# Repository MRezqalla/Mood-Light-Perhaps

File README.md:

# Mood-Light-Perhaps
## This project concerns a mood light arduino device that can change moods. 
### Maybe in the future expand it so it's perhaps.

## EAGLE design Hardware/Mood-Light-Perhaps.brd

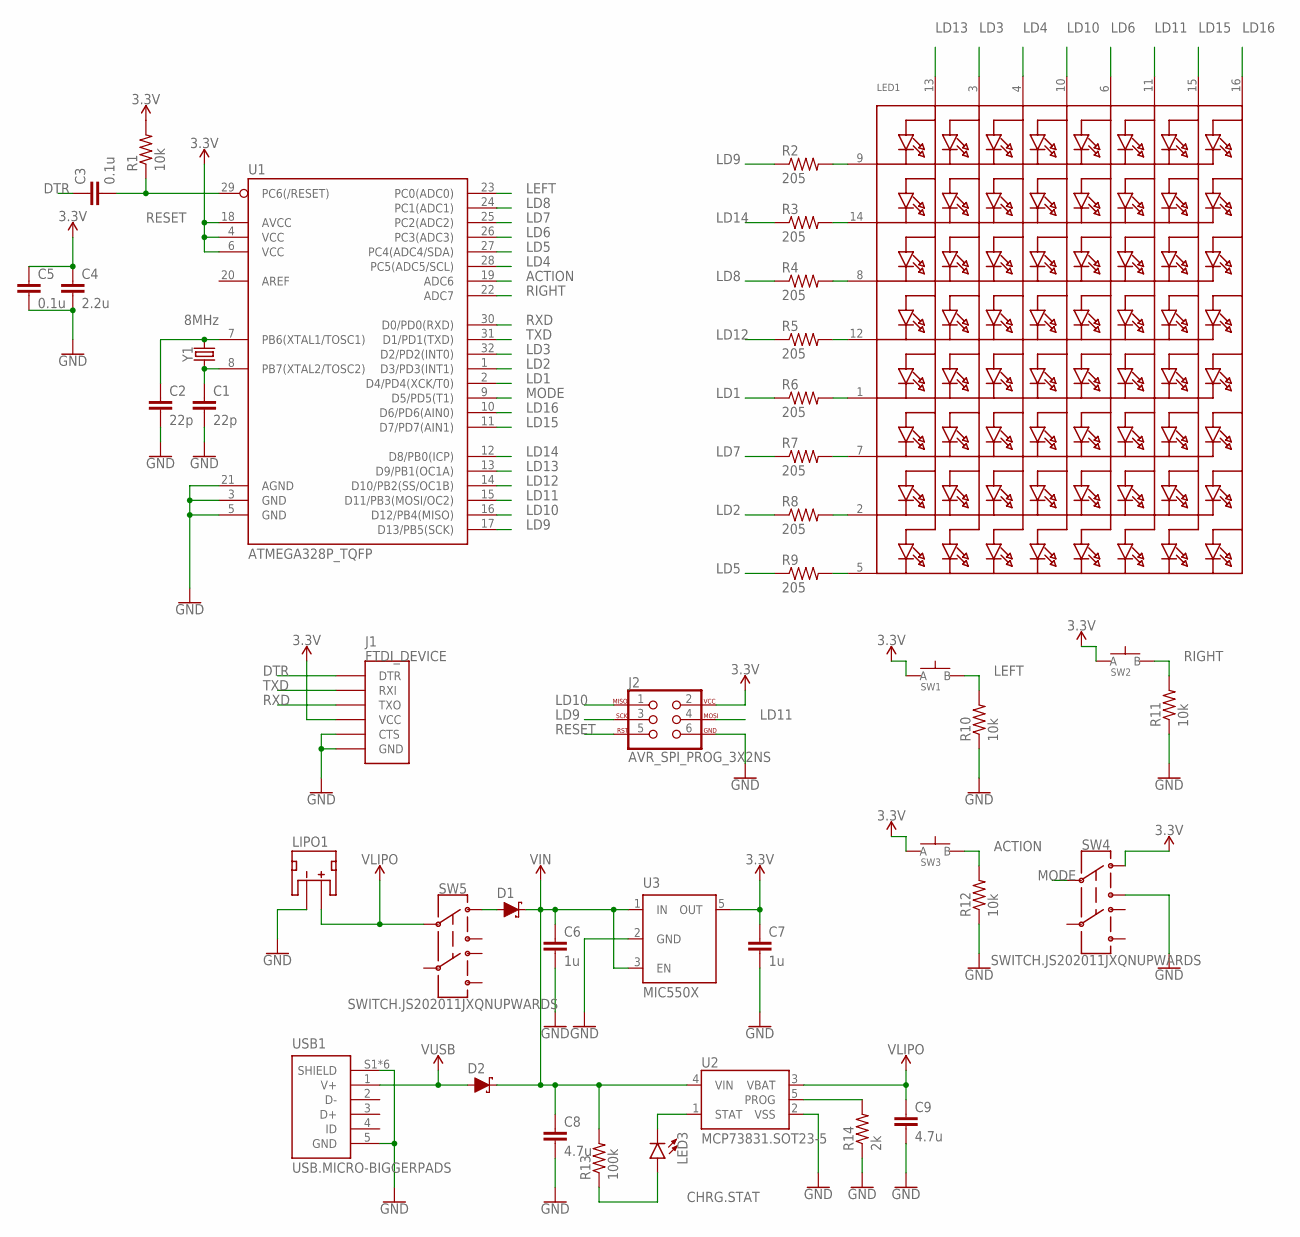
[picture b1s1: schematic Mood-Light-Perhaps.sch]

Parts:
C1, C2: 22p; C0603
C3, C5: 0.1u; C0603
C4: 2.2u; C0603
C6, C7: 1u; C0603
C8, C9: 4.7u; C0603
D1, D2: SCHOTTKY-USC; USC
J1: FTDI_DEVICE
J2: AVR_SPI_PROG_3X2NS; 2X3-NS
LED1: DOTMATRIX_8X8_ROWCATHODEM12A881UR; DOTMATRIX_BL-M12A881UR
LED3: LED0805; LED-0805
LIPO1: JST_2MM_MALE; JST-2-SMD
R1, R10, R11, R12: 10k; R0603
R2, R3, R4, R5, R6, R7, R8, R9: 205; R0603
R13: 100k; R0603
R14: 2k; R0603
SW1, SW2, SW3: SPST.KT11P4SM34LFS
SW4, SW5: SWITCH.JS202011JXQNUPWARDS; SWITCH.00
U1: ATMEGA328P_TQFP; TQFP32-08
U2: MCP73831.SOT23-5; SOT23-5
U3: MIC550X; SOT23-5
USB1: USB.MICRO-BIGGERPADS; USB-MICRO-01.BIGGERPADS
Y1: 8MHz; CA-301

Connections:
3.3V: C4.1, C5.1, C7.1, J1.VCC, J2.2, R1.2, SW1.1 (A), SW1.2 (A), SW2.1 (A), SW2.2 (A), SW3.1 (A), SW3.2 (A), SW4.1, U1.4 (VCC), U1.6 (VCC), U1.18 (AVCC), U3.5 (OUT)
ACTION: R12.2, SW3.3 (B), SW3.4 (B), U1.19 (ADC6)
CHRG.STAT: LED3.A, R13.1
DTR: C3.1, J1.DTR
GND: C1.2, C2.2, C4.2, C5.2, C6.2, C7.2, C8.2, C9.2, J1.CTS, J1.GND, J2.6, LIPO1.1 (-), R10.1, R11.1, R12.1, R14.1, SW4.3, U1.3 (GND), U1.5 (GND), U1.21 (AGND), U2.2 (VSS), U3.2 (GND), USB1.5 (GND), USB1.S1 (SHIELD), USB1.S2 (SHIELD), USB1.S3 (SHIELD), USB1.S4 (SHIELD), USB1.S5 (SHIELD), USB1.S6 (SHIELD)
LD1: R6.1, U1.2 (D4/PD4(XCK/T0))
LD2: R8.1, U1.1 (D3/PD3(INT1))
LD3: LED1.3 (A2), U1.32 (D2/PD2(INT0))
LD4: LED1.4 (A3), U1.28 (PC5(ADC5/SCL))
LD5: R9.1, U1.27 (PC4(ADC4/SDA))
LD6: LED1.6 (A5), U1.26 (PC3(ADC3))
LD7: R7.1, U1.25 (PC2(ADC2))
LD8: R4.1, U1.24 (PC1(ADC1))
LD9: J2.3, R2.1, U1.17 (D13/PB5(SCK))
LD10: J2.1, LED1.10 (A4), U1.16 (D12/PB4(MISO))
LD11: J2.4, LED1.11 (A6), U1.15 (D11/PB3(MOSI/OC2))
LD12: R5.1, U1.14 (D10/PB2(SS/OC1B))
LD13: LED1.13 (A1), U1.13 (D9/PB1(OC1A))
LD14: R3.1, U1.12 (D8/PB0(ICP))
LD15: LED1.15 (A7), U1.11 (D7/PD7(AIN1))
LD16: LED1.16 (A8), U1.10 (D6/PD6(AIN0))
LEFT: R10.2, SW1.3 (B), SW1.4 (B), U1.23 (PC0(ADC0))
MODE: SW4.2, U1.9 (D5/PD5(T1))
unnamed: LED1.9 (K1), R2.2
unnamed: C2.1, U1.7 (PB6(XTAL1/TOSC1)), Y1.2
unnamed: C1.1, U1.8 (PB7(XTAL2/TOSC2)), Y1.1
unnamed: LED1.14 (K2), R3.2
unnamed: LED1.8 (K3), R4.2
unnamed: LED1.12 (K4), R5.2
unnamed: LED1.1 (K5), R6.2
unnamed: LED1.7 (K6), R7.2
unnamed: LED1.2 (K7), R8.2
unnamed: LED1.5 (K8), R9.2
unnamed: R14.2, U2.5 (PROG)
unnamed: D1.+ (A), SW5.1
unnamed: LED3.C, U2.1 (STAT)
RESET: C3.2, J2.5, R1.1, U1.29 (PC6(/RESET))
RIGHT: R11.2, SW2.3 (B), SW2.4 (B), U1.22 (ADC7)
RXD: J1.RXI (TXO), U1.30 (D0/PD0(RXD))
TXD: J1.TXO (RXI), U1.31 (D1/PD1(TXD))
VIN: C6.1, C8.1, D1.- (C), D2.- (C), R13.2, U2.4 (VIN), U3.1 (IN), U3.3 (EN)
VLIPO: C9.1, LIPO1.2 (+), SW5.2, U2.3 (VBAT)
V_USB: D2.+ (A), USB1.1 (V+)

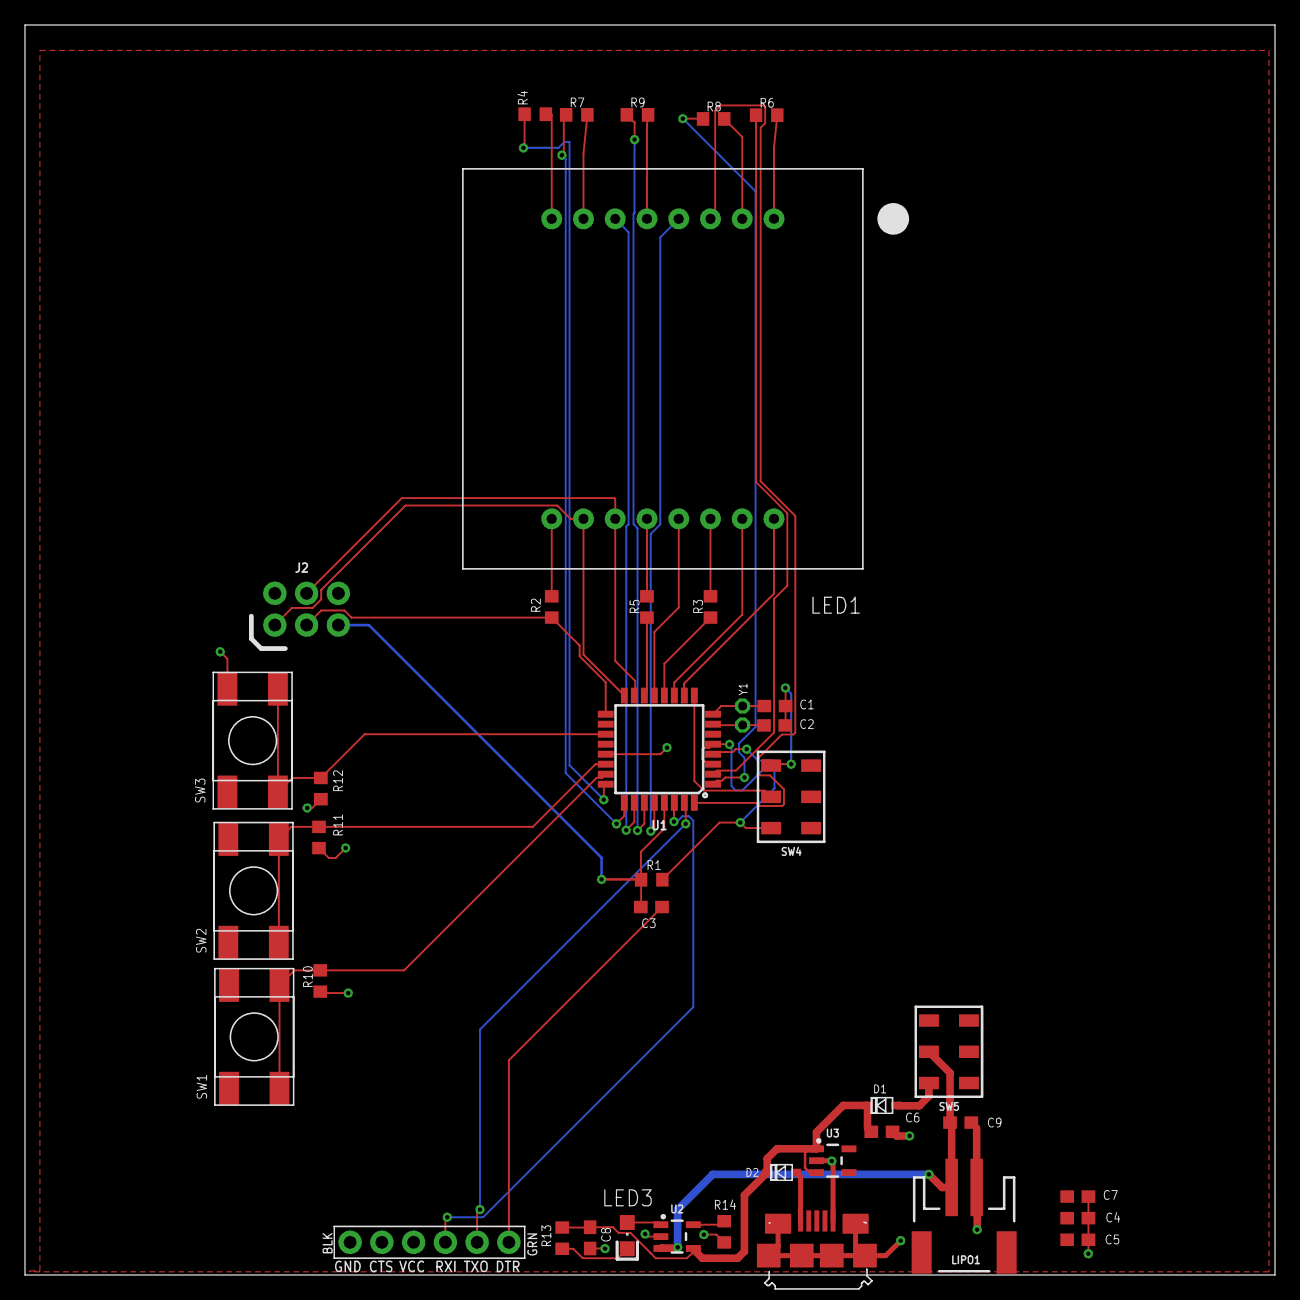
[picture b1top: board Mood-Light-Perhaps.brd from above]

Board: 2 copper layers, 100.0 x 100.0 mm, 40 parts (0 on the bottom side), 43 nets.

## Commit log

2022-09-07 Features? List
2022-09-14 Organization
2022-09-14 Progress made
2022-09-28 Finished schematic
2022-09-28 Board progress 1
2022-09-28 Board progress 2
2022-09-28 test
2022-09-28 Changed LED
2022-09-28 Progress 3
2022-09-28 Progress 4
2022-09-29 Progress 6? need to fix errors
2022-09-29 Completed PCB
2022-10-19 edited board and added CAM outputs
2022-10-19 updated GERBERs for FTDI silkscreen
2022-11-09 Updated BOM Part 1
